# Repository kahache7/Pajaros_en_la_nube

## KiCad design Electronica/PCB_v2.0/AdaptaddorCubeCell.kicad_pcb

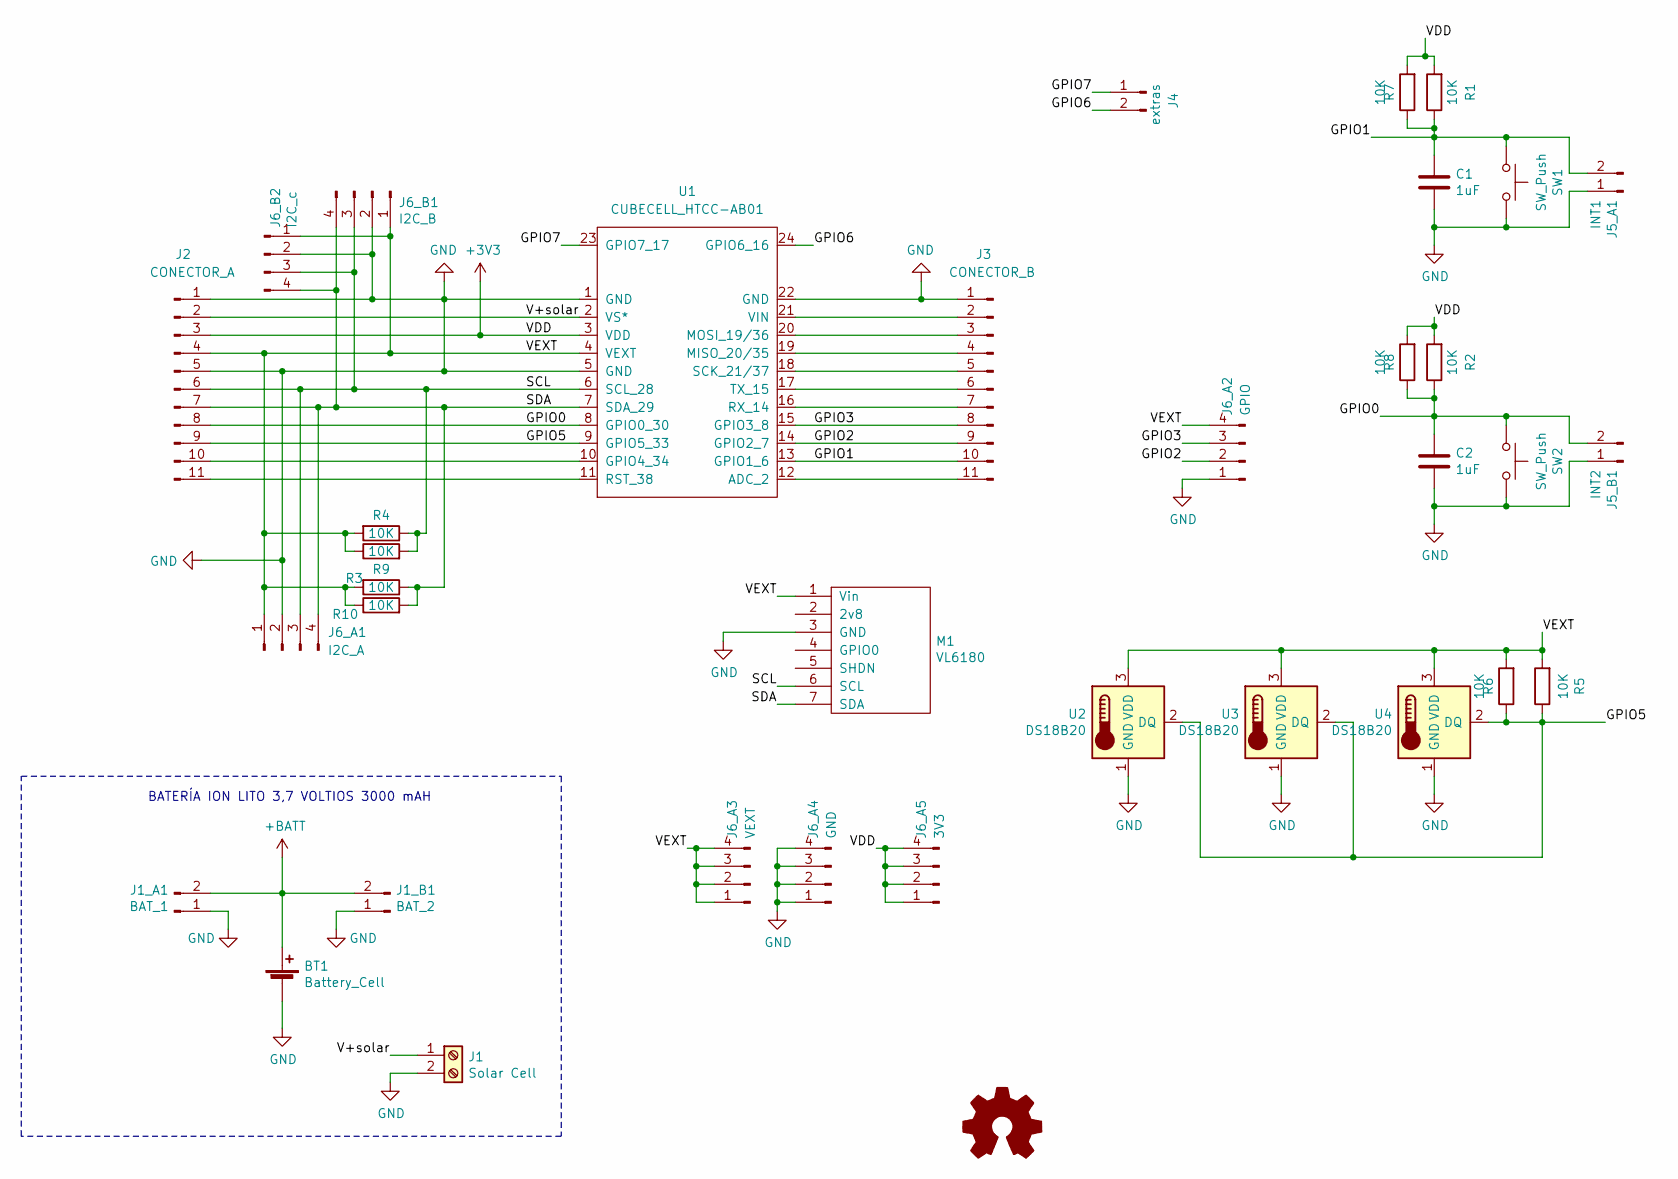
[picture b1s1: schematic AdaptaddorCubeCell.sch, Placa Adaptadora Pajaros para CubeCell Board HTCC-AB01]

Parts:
BT1: Battery_Cell; BatteryHolder_MPD_BH-18650-PC2
C1, C2: 1uF; C_Disc_D5.0mm_W2.5mm_P5.00mm
J1: Solar Cell; TerminalBlock_bornier-2_P5.08mm
J1_A1: BAT_1; PinHeader_1x02_P2.54mm_Vertical_custom
J1_B1: BAT_2; PinHeader_1x02_P2.54mm_Vertical_custom
J2: CONECTOR_A; PinHeader_1x11_P2.54mm_Vertical
J3: CONECTOR_B; PinHeader_1x11_P2.54mm_Vertical
J4: extras; PinHeader_1x02_P2.54mm_Vertical_custom
J5_A1: INT1; PinHeader_1x02_P2.54mm_Vertical_custom
J5_B1: INT2; PinHeader_1x02_P2.54mm_Vertical_custom
J6_A1: I2C_A; PinHeader_1x04_P2.54mm_Vertical
J6_A2: GPIO; PinHeader_1x04_P2.54mm_Vertical
J6_A3: VEXT; PinHeader_1x04_P2.54mm_Vertical
J6_A4: GND; PinHeader_1x04_P2.54mm_Vertical
J6_A5: 3V3; PinHeader_1x04_P2.54mm_Vertical
J6_B1: I2C_B; PinHeader_1x04_P2.54mm_Vertical
J6_B2: I2C_c; PinHeader_1x04_P2.54mm_Vertical
M1: VL6180; VL6180x
R1, R2, R3, R4, R5: 10K; R_Axial_DIN0207_L6.3mm_D2.5mm_P7.62mm_Horizontal
R6, R7, R8, R9, R10: 10K; R_1206_HandSoldering
SW1, SW2: SW_Push; SW_PUSH_6mm_H5mm
U1: CUBECELL_HTCC-AB01; CubeCell_HTCC-AB01
U2, U3, U4: DS18B20; TO-92_Inline_Narrow_Oval

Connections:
+3V3: J2.3, J6_A5.1, J6_A5.2, J6_A5.3, J6_A5.4, R1.2, R2.2, R7.2, R8.2, U1.3 (VDD)
+BATT: BT1.1 (+), J1_A1.2, J1_B1.2
/GPIO0: C2.1, J2.8, J5_B1.2, R2.1, R8.1, SW2.1, U1.8 (GPIO0_30)
/GPIO1: C1.1, J3.10, J5_A1.2, R1.1, R7.1, SW1.1, U1.13 (GPIO1_6)
/GPIO2: J3.9, J6_A2.2, U1.14 (GPIO2_7)
/GPIO3: J3.8, J6_A2.3, U1.15 (GPIO3_8)
/GPIO5: J2.9, R5.1, R6.1, U1.9 (GPIO5_33), U2.2 (DQ), U3.2 (DQ), U4.2 (DQ)
/GPIO6: J4.2, U1.24 (GPIO6_16)
/GPIO7: J4.1, U1.23 (GPIO7_17)
/SCL: J2.6, J6_A1.3, J6_B1.3, J6_B2.3, M1.6 (SCL), R4.1, R9.2, U1.6 (SCL_28)
/SDA: J2.7, J6_A1.4, J6_B1.4, J6_B2.4, M1.7 (SDA), R3.1, R10.2, U1.7 (SDA_29)
/V+solar: J1.1, J2.2, U1.2 (VS*)
/VEXT: J2.4, J6_A1.1, J6_A2.4, J6_A3.1, J6_A3.2, J6_A3.3, J6_A3.4, J6_B1.1, J6_B2.1, M1.1 (Vin), R3.2, R4.2, R5.2, R6.2, R9.1, R10.1, U1.4 (VEXT), U2.3 (VDD), U3.3 (VDD), U4.3 (VDD)
GND: BT1.2 (-), C1.2, C2.2, J1.2, J1_A1.1, J1_B1.1, J2.1, J2.5, J3.1, J5_A1.1, J5_B1.1, J6_A1.2, J6_A2.1, J6_A4.1, J6_A4.2, J6_A4.3, J6_A4.4, J6_B1.2, J6_B2.2, M1.3 (GND), SW1.2, SW2.2, U1.1 (GND), U1.5 (GND), U1.22 (GND), U2.1 (GND), U3.1 (GND), U4.1 (GND)
unnamed: J2.10, U1.10 (GPIO4_34)
unnamed: J2.11, U1.11 (RST_38)
unnamed: J3.2, U1.21 (VIN)
unnamed: J3.3, U1.20 (MOSI_19/36)
unnamed: J3.4, U1.19 (MISO_20/35)
unnamed: J3.5, U1.18 (SCK_21/37)
unnamed: J3.6, U1.17 (TX_15)
unnamed: J3.7, U1.16 (RX_14)
unnamed: J3.11, U1.12 (ADC_2)

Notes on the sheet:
BATERÍA ION LITO 3,7 VOLTIOS 3000 mAH

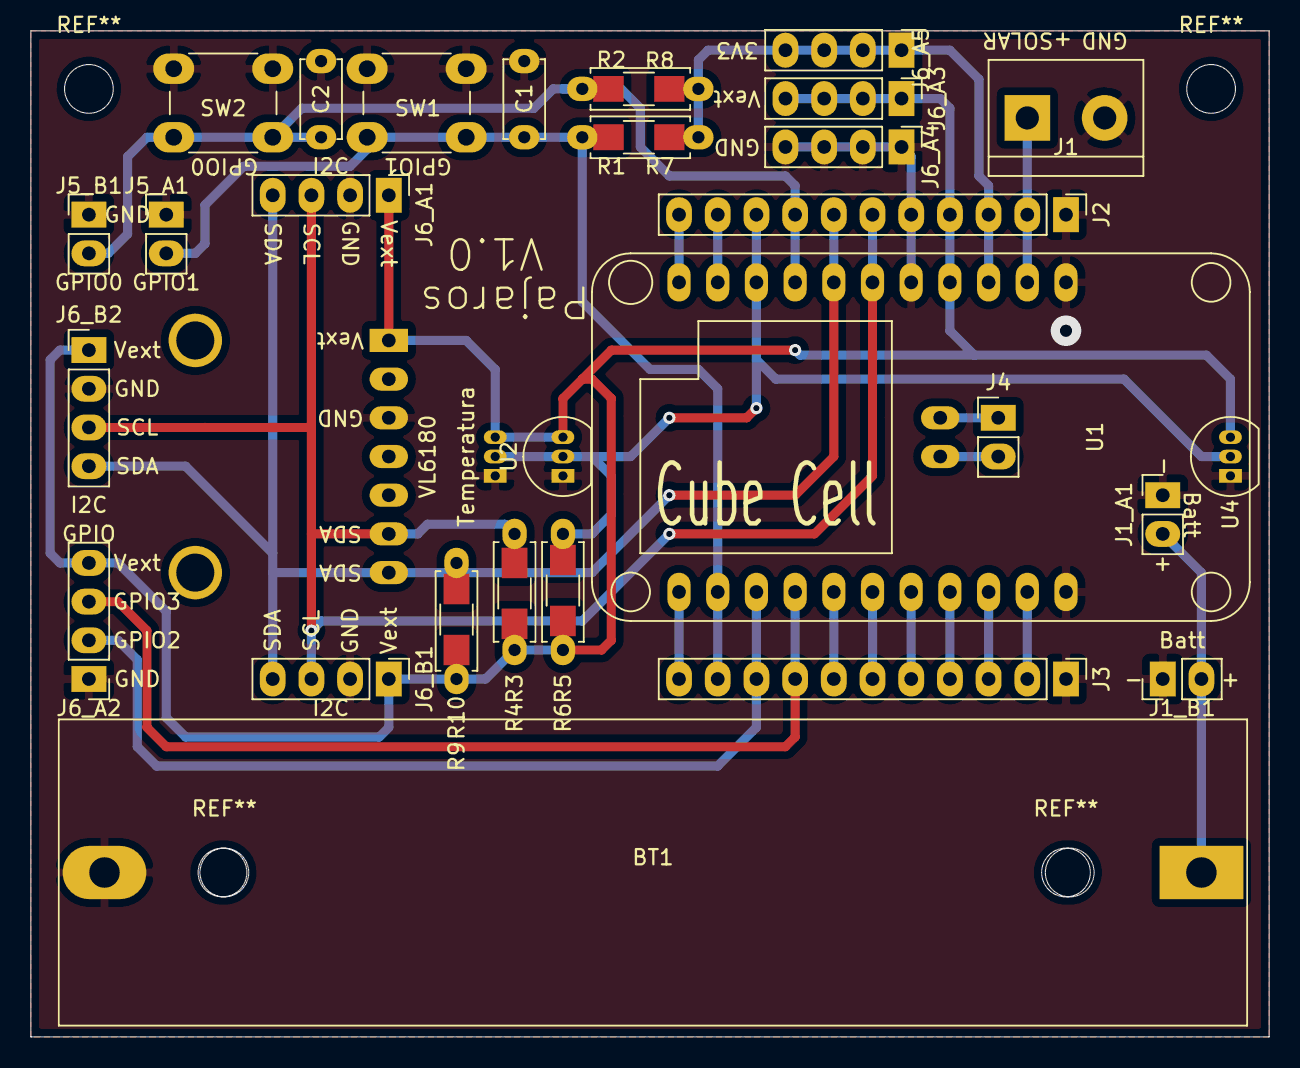
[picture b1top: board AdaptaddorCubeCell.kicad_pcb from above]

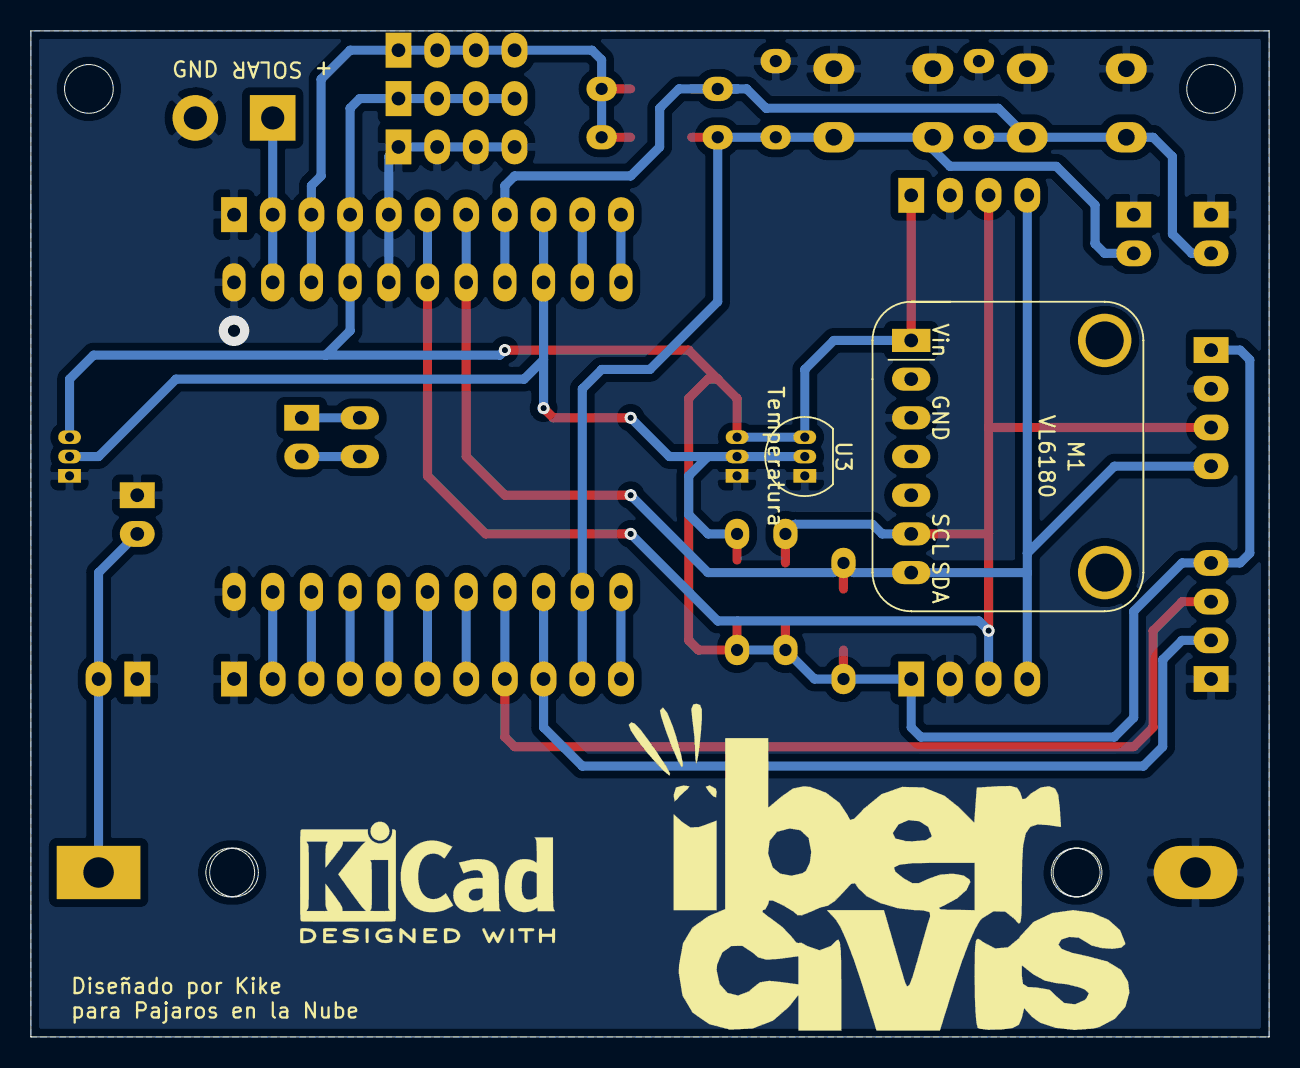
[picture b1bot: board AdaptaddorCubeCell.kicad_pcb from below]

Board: 2 copper layers, 81.3 x 66.0 mm, 35 parts (2 on the bottom side), 23 nets.

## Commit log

2020-11-09 primer version
2021-03-05 Create fp-lib-table
2021-03-05 Create sym-lib-table
